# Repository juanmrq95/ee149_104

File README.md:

# ee149_104
EE149 project

ASL Glove:

We created a glove able to interpret every gesture in the ASL alphabet and translate it to text and speech.
We did so by putting touch and flex sensors as well as an IMU embedded on the glove. We designed a sensing circuit 
embedded on the backside of the glove on a flexible PCB sheet as well a small PCB for interfacing with our microprocessor
placed on the wrist.

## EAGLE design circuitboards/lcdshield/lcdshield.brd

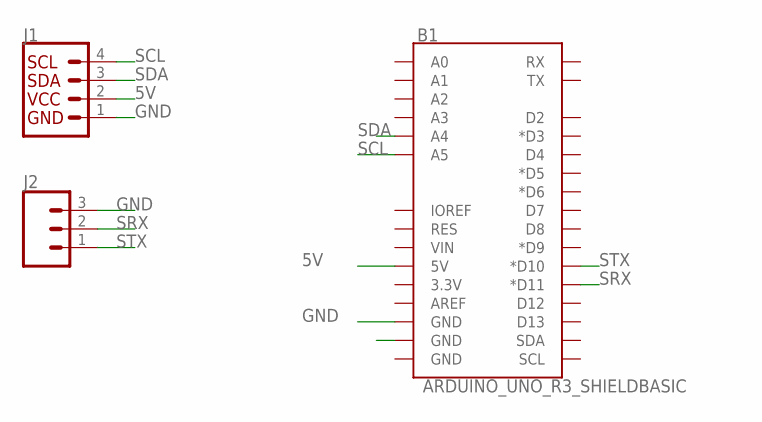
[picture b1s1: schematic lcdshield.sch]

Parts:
B1: ARDUINO_UNO_R3_SHIELDBASIC; UNO_R3_SHIELD
J1: I2C_STANDARD; 1X04
J2: CONN_03; 1X03

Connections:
5V: B1.5V, J1.2
GND: B1.GND@1 (GND), B1.GND@2 (GND), J1.1, J2.3
SCL: B1.A5, J1.4
SDA: B1.A4, J1.3
SRX: B1.D11 (*D11), J2.2
STX: B1.D10 (*D10), J2.1

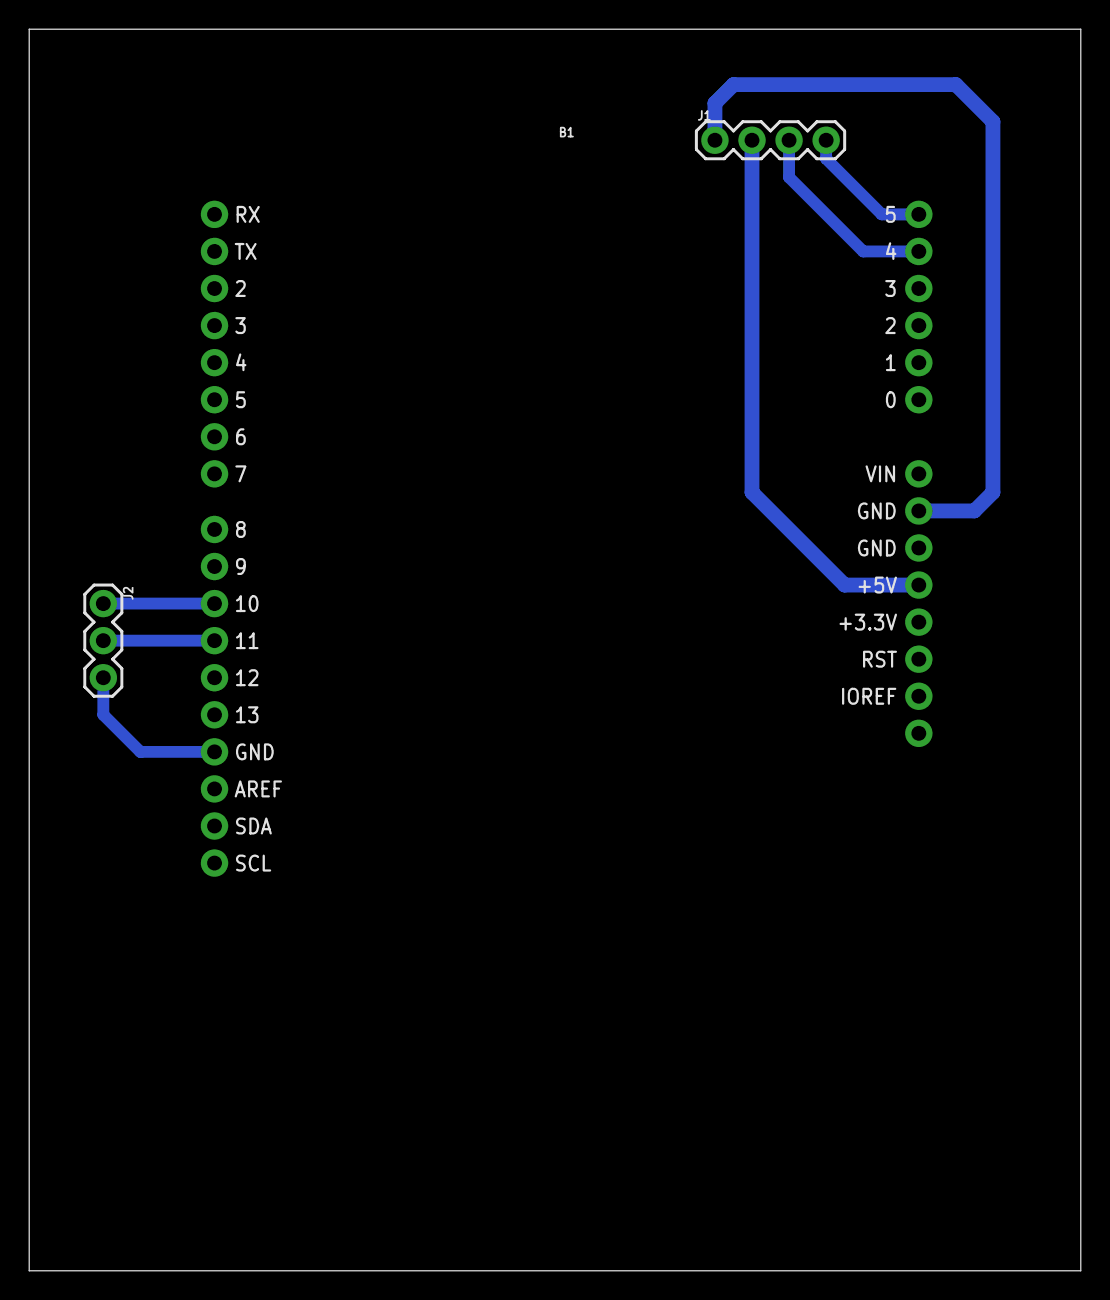
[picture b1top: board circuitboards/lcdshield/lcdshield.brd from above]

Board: 2 copper layers, 72.1 x 85.1 mm, 3 parts (0 on the bottom side), 6 nets.

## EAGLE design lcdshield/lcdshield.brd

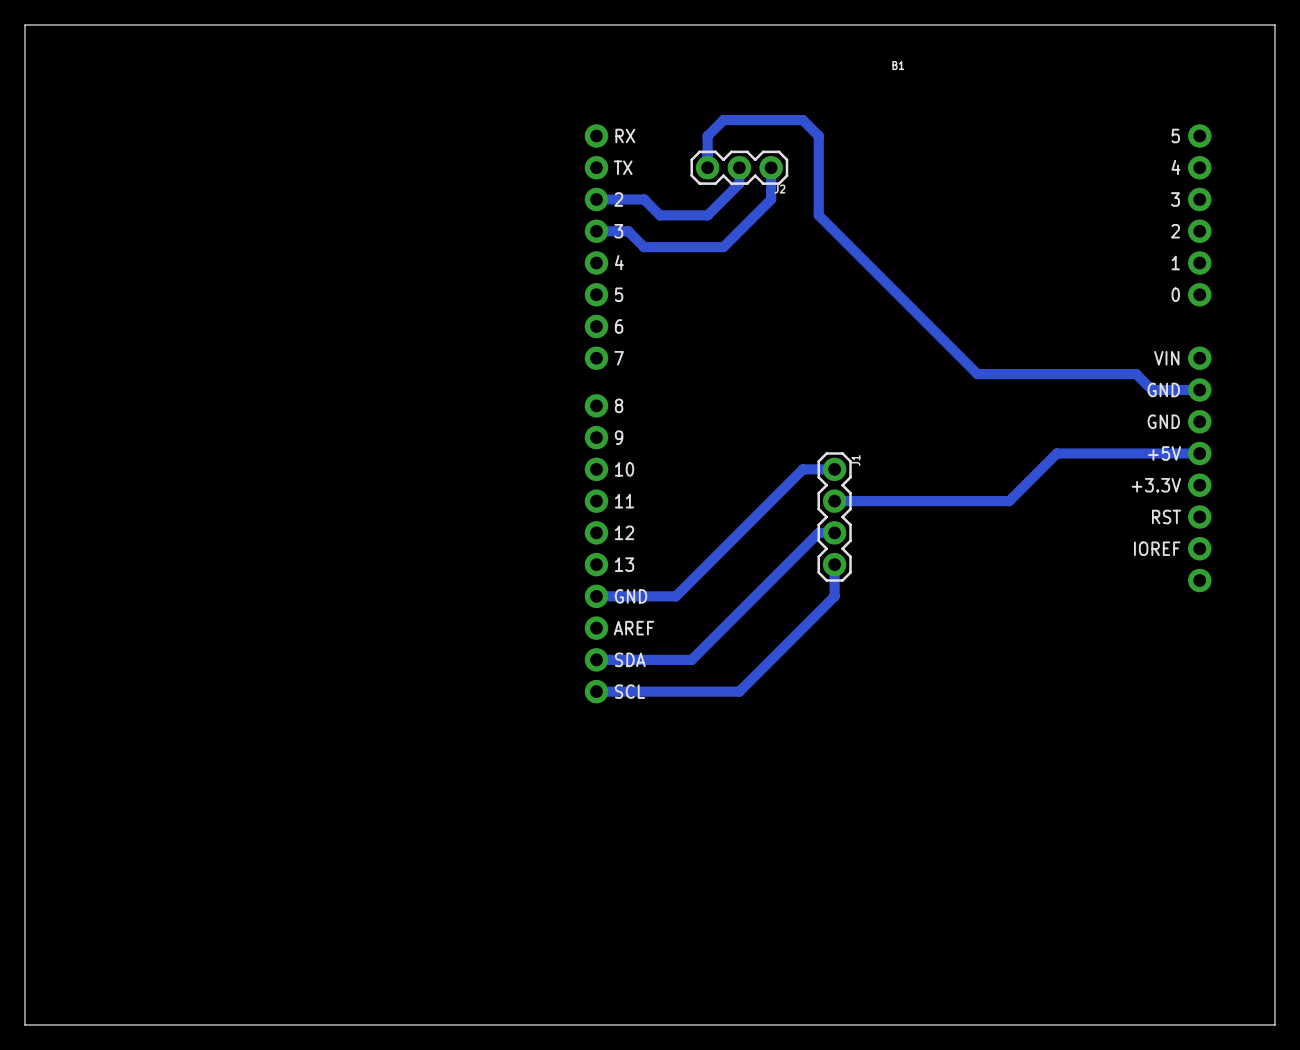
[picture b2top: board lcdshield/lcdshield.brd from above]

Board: 2 copper layers, 100.0 x 80.0 mm, 3 parts (0 on the bottom side), 6 nets.

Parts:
B1: ARDUINO_UNO_R3_SHIELDBASIC; UNO_R3_SHIELD
J1: 1X04
J2: 1X03

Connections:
5V: B1.5V, J1.2
GND: B1.GND@0, B1.GND@1, B1.GND@2, J1.1, J2.3
SCL: B1.SCL, J1.4
SDA: B1.SDA, J1.3
SRX: B1.D3, J2.1
STX: B1.D2, J2.2

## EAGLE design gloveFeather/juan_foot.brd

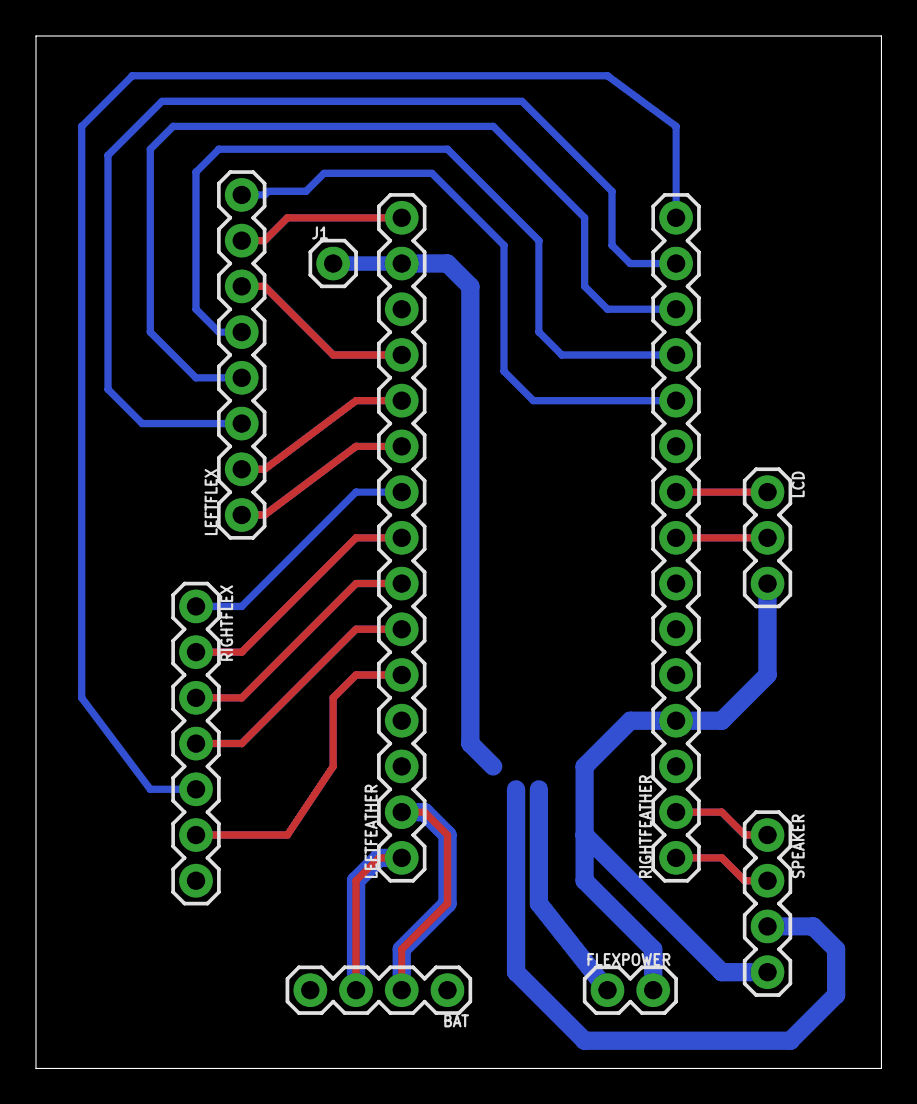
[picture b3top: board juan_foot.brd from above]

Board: 2 copper layers, 47.0 x 57.4 mm, 9 parts (0 on the bottom side), 22 nets.

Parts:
BAT: 1X04
FLEXPOWER: 1X02
J1: 1X01
LCD: 1X03
LEFTFEATHER: 1X15
LEFTFLEX: 1X08
RIGHTFEATHER: 1X15
RIGHTFLEX: 1X07
SPEAKER: 1X04

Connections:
3V: FLEXPOWER.1, J1.1, LEFTFEATHER.14, SPEAKER.3
GND: BAT.2, FLEXPOWER.2, LCD.3, LEFTFEATHER.2, RIGHTFEATHER.4, SPEAKER.4
INDEXFLEX: LEFTFEATHER.11, LEFTFLEX.2
INDEXSIDE: LEFTFEATHER.9, RIGHTFLEX.1
INDEXTIP: LEFTFLEX.3, RIGHTFEATHER.14
MIDDLEB: LEFTFLEX.5, RIGHTFEATHER.12
MIDDLEFLEX: LEFTFEATHER.12, LEFTFLEX.6
MIDDLESIDE: LEFTFLEX.4, RIGHTFEATHER.13
MIDDLETIP: LEFTFEATHER.15, LEFTFLEX.7
PINKYFLEX: LEFTFEATHER.5, RIGHTFLEX.6
PINKYSIDE: RIGHTFEATHER.15, RIGHTFLEX.5
RINGFLEX: LEFTFEATHER.6, RIGHTFLEX.4
RINGSIDE: LEFTFLEX.8, RIGHTFEATHER.11
RST: LEFTFEATHER.3, RIGHTFEATHER.3
SCL: LEFTFEATHER.7, RIGHTFLEX.3
SDA: LEFTFEATHER.8, RIGHTFLEX.2
SIN: RIGHTFEATHER.2, SPEAKER.1
SOUT: RIGHTFEATHER.1, SPEAKER.2
SRX: LCD.1, RIGHTFEATHER.9
STX: LCD.2, RIGHTFEATHER.8
THUMBFLEX: LEFTFEATHER.10, LEFTFLEX.1
VIN: BAT.3, LEFTFEATHER.1

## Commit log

2017-11-09 ABCD
2017-11-10 Code for pause at letter and both touch sensors
2017-11-13 Add Glove State Machine
2017-11-13 reviewed code
2017-11-14 added calibration on glove 2.0
2017-11-15 added mac speech
2017-11-16 Demo Code
2017-11-19 Add Basic State Machine
2017-11-20 Updat State Machine for Classification
2017-11-20 Add Desicion tree test implementation in Python
2017-11-23 added code for textToSpeech board
2017-11-28 Added Accel/Gyro code in accel/accel.ino
2017-11-30 speech module
2017-12-01 Add Output test features - text to speech & 16x2 LCD Display
2017-12-02 Update LCD Module
2017-12-02 pcb testing
2017-12-02 Add library file for LCD Module
2017-12-03 feather pcb locoooos
2017-12-03 pcb for nano almost ready
2017-12-03 Added Ground Plane
2017-12-04 pcb updated with new connections. Added 3V plane
2017-12-06 finished glove pcb and speaker pcb
2017-12-08 Add glove module and alphabet datasets
2017-12-09 Add Edit Function Datasets and Add PCB Test Base Code
2017-12-09 final pcb
2017-12-09 Add Glove final module code
2017-12-09 verified outputs from PCB work. errthing work w/o computerrr
2017-12-10 SM with A-M
2017-12-11 added all code with working state machine + non-accel letters
2017-12-12 LCD serial
2017-12-12 nano to lcd done!
2017-12-13 working code is: ...battery_speech
2017-12-13 calibrated values for aashyk, a-z (without accel) and enter edit mode, but without changes to edit functions
2017-12-14 ginal version

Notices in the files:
parts and their libraries:
SparkFun-Boards: Licensing: Creative Commons ShareAlike 4.0 International - https://creativecommons.org/licenses/by-sa/4.0
